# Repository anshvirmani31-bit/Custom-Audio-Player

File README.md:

# Custom-Audio-Player
Plays custom audio when you touch/click certain parts and things. The auido files it plays must be compressed as there is no external sd card slot, it is based of an esp32

# What is it?

This is a small audio file player with it's own standalone speaker based of an ESP-32-S3-WROOM-1. You can insert your own audio files however it has no external SD card slot meaning you only get the amount of local storage available on the ESP-32. This could be a potential downside because your file(s) will have to be heavily compressed. The reason I chose to design it like this is to keep the cost down and simpler to design.

# Images

## Schematic

### Full Schematic

### Oled Screen

### Rotary Encoder

### Voltage Regulator

### Audio Amplifier

### ESP32

### Receptacle

### Capacitive Touch Pads

### Cherry MX Button

## PCB

### Full Pcb

### 3D View

#### Front

#### Back

# BOM

|Item                       |Qty|Supplier  |Cost/item|Total Cost|link                                                 |
|---------------------------|---|----------|---------|----------|-----------------------------------------------------|
|ESP32-S3-WROOM1            |1  |AliExpress|$1.09    |$1.09     |https://www.aliexpress.com/item/1005010196291979.html|
|AP2112K-3.3TRG1            |1  |AliExpress|$1.89    |$1.89     |https://www.aliexpress.com/item/1005009023441155.html|
|MAX98357AETE+T             |1  |AliExpress|$6.44    |$6.44     |https://www.aliexpress.com/item/1005013004267095.html|
|USB Connector Type C Female|1  |AliExpress|$4.81    |$4.81     |https://www.aliexpress.com/item/1005013012638787.html|
|Rotary Encoder             |1  |AliExpress|$1.91    |$1.91     |https://www.aliexpress.com/item/1005007644083514.html|
|4 ohm Speaker              |1  |AliExpress|$2.28    |$2.28     |https://www.aliexpress.com/item/1005008626624201.html|
|Resistors                  |1  |AliExpress|$4.75    |$4.75     |https://www.aliexpress.com/item/1005012948787921.html|
|PCB                        |1  |JLCPCB    |$4.00    |$4.00     |https://jlcpcb.com                                   |
|OLED                       |1  |AliExpress|$2.55    |$2.55     |https://www.aliexpress.com/item/1005005692457058.html|
|Estimated total shipping   |1  |          |         |$1.50     |                                                     |

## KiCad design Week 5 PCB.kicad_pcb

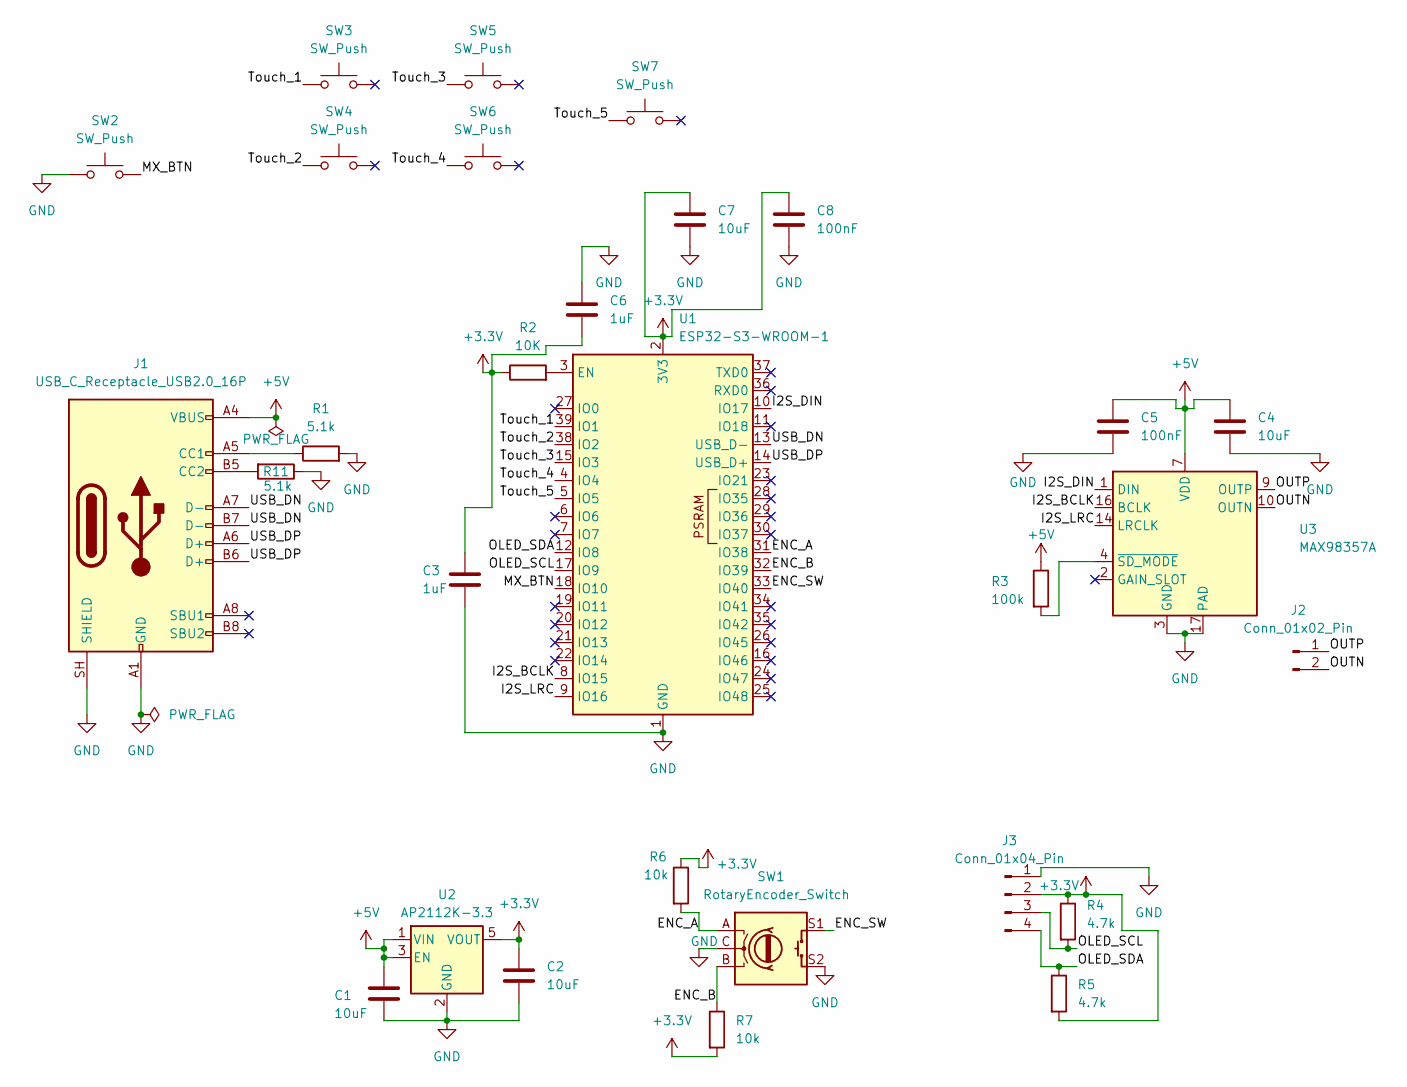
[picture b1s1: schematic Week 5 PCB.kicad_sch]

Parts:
C1, C2, C4, C7: 10uF; C_0805_2012Metric
C3, C6: 1uF; C_0805_2012Metric
C5, C8: 100nF; C_0805_2012Metric
J1: USB_C_Receptacle_USB2.0_16P; USB_C_Receptacle_HRO_TYPE-C-31-M-12
J2: Conn_01x02_Pin; PinHeader_1x02_P2.54mm_Vertical
J3: Conn_01x04_Pin; PinHeader_1x04_P2.54mm_Vertical
R1, R11: 5.1k; R_0805_2012Metric
R2: 10K; R_0805_2012Metric
R3: 100k; R_0805_2012Metric
R4, R5: 4.7k; R_0805_2012Metric
R6, R7: 10k; R_0805_2012Metric
SW1: RotaryEncoder_Switch; RotaryEncoder_Alps_EC11E-Switch_Vertical_H20mm
SW2: SW_Push; SW_Cherry_MX_1.00u_PCB
SW3, SW4, SW5, SW6, SW7: SW_Push; Single Touchpad
U1: ESP32-S3-WROOM-1
U2: AP2112K-3.3; SOT-23-5
U3: MAX98357A; TQFN-16-1EP_3x3mm_P0.5mm_EP1.23x1.23mm

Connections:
+3.3V: C2.1, C3.1, C6.2, C7.1, C8.1, J3.2, R2.1, R4.1, R5.2, R6.1, R7.2, U1.2 (3V3), U2.5 (VOUT)
+5V: C1.1, C4.1, C5.1, J1.A4 (VBUS), J1.A9 (VBUS), J1.B4 (VBUS), J1.B9 (VBUS), R3.1, U2.1 (VIN), U2.3 (EN), U3.7 (VDD), U3.8 (VDD)
/ENC_A: R6.2, SW1.A, U1.31 (IO38)
/ENC_B: R7.1, SW1.B, U1.32 (IO39)
/ENC_SW: SW1.S1, U1.33 (IO40)
/I2S_BCLK: U1.8 (IO15), U3.16 (BCLK)
/I2S_DIN: U1.10 (IO17), U3.1 (DIN)
/I2S_LRC: U1.9 (IO16), U3.14 (LRCLK)
/MX_BTN: SW2.2, U1.18 (IO10)
/OLED_SCL: J3.3, R4.2, U1.17 (IO9)
/OLED_SDA: J3.4, R5.1, U1.12 (IO8)
/OUTN: J2.2, U3.10 (OUTN)
/OUTP: J2.1, U3.9 (OUTP)
/Touch_1: SW3.1 (1_1), U1.39 (IO1)
/Touch_2: SW4.1 (1_1), U1.38 (IO2)
/Touch_3: SW5.1 (1_1), U1.15 (IO3)
/Touch_4: SW6.1 (1_1), U1.4 (IO4)
/Touch_5: SW7.1 (1_1), U1.5 (IO5)
/USB_DN: J1.A7 (D-), J1.B7 (D-), U1.13 (USB_D-)
/USB_DP: J1.A6 (D+), J1.B6 (D+), U1.14 (USB_D+)
GND: C1.2, C2.2, C3.2, C4.2, C5.2, C6.1, C7.2, C8.2, J1.A1 (GND), J1.A12 (GND), J1.B1 (GND), J1.B12 (GND), J1.SH (SHIELD), J3.1, R1.2, R11.1, SW1.C, SW1.S2, SW2.1, U1.1 (GND), U1.40 (GND), U1.41 (GND), U2.2 (GND), U3.3 (GND), U3.11 (GND), U3.15 (GND), U3.17 (PAD)
unnamed: J1.A5 (CC1), R1.1
unnamed: J1.B5 (CC2), R11.2
unnamed: R2.2, U1.3 (EN)
unnamed: R3.2, U3.4 (~SD_MODE)

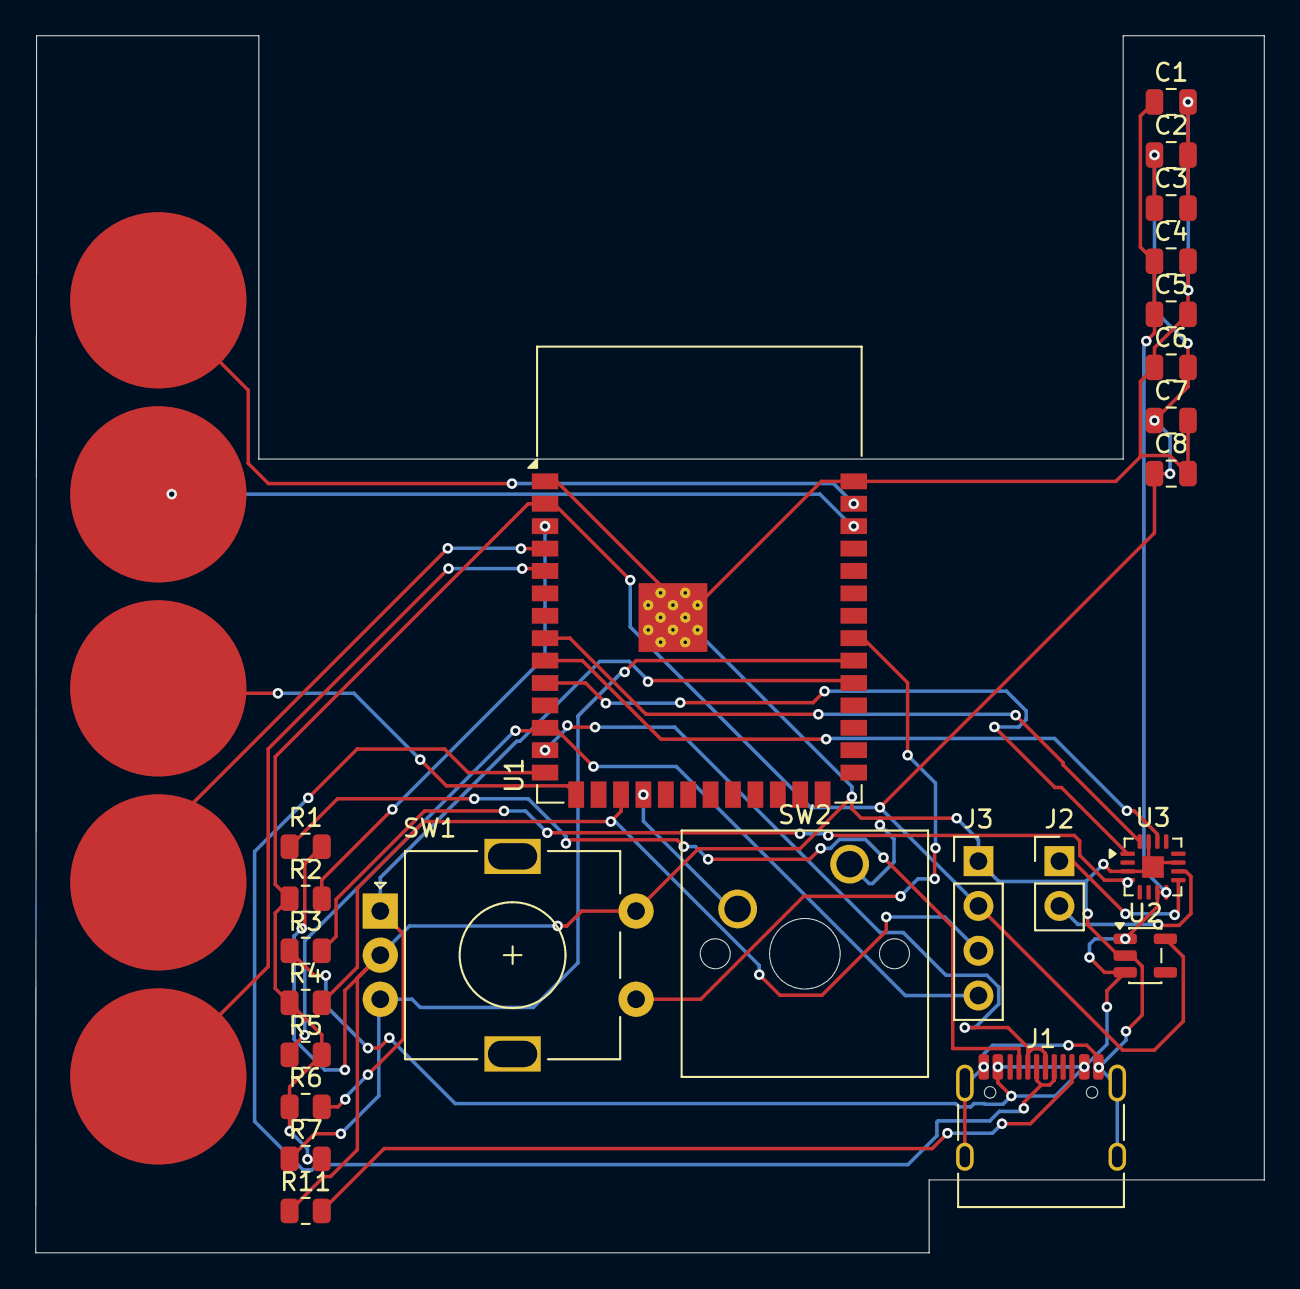
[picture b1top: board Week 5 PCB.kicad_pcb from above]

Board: 2 copper layers, 69.7 x 69.0 mm, 29 parts (0 on the bottom side), 25 nets.

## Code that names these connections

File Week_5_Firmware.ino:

#include <Arduino.h>
#include <Wire.h>
#include <LittleFS.h>
#include <Adafruit_GFX.h>
#include <Adafruit_SSD1306.h>
#include <ESP32Encoder.h>
#include "Audio.h"

// 1. Pin appointing

// MAX98357A I2S Amplifier (U3)
#define I2S_BCLK      15  // Pin 8 on U1 -> I2S_BCLK
#define I2S_LRC       16  // Pin 9 on U1 -> I2S_LRC
#define I2S_DOUT      17  // Pin 10 on U1 -> I2S_DIN

// Rotary Encoder (SW1)
#define ENC_A         38  // Pin 31 on U1 -> ENC_A
#define ENC_B         39  // Pin 32 on U1 -> ENC_B
#define ENC_SW        40  // Pin 33 on U1 -> ENC_SW

// Cherry MX Mechanical Switch (SW2)
#define MX_BTN_PIN    10  // Pin 18 on U1 -> MX_BTN

// I2C OLED Display (J3)
#define OLED_SDA      8   // Pin 12 on U1 -> OLED_SDA
#define OLED_SCL      9   // Pin 13 on U1 -> OLED_SCL
#define SCREEN_WIDTH  128
#define SCREEN_HEIGHT 64
#define OLED_ADDR     0x3C

// 5 Capacitive Touch Pads (SW3 - SW7)
const int TOUCH_PINS[5] = {1, 2, 3, 4, 5}; // IO1..IO5
const char* SOUND_FILES[5] = {
  "/sound1.mp3",
  "/sound2.mp3",
  "/sound3.mp3",
  "/sound4.mp3",
  "/sound5.mp3"
};
const char* SOUND_NAMES[5] = {
  "Pad 1: Track 1",
  "Pad 2: Track 2",
  "Pad 3: Track 3",
  "Pad 4: Track 4",
  "Pad 5: Track 5"
};

// 2. Objects
Audio audio;
ESP32Encoder encoder;
Adafruit_SSD1306 display(SCREEN_WIDTH, SCREEN_HEIGHT, &Wire, -1);

int currentVolume = 12;          // Range: 0 to 21
int savedVolume = 12;            // Stores pre-mute volume
bool isMuted = false;
const int MAX_VOLUME = 21;
long lastEncoderPos = 0;

String currentTrack = "Ready";
bool oledAvailable = false;

uint32_t touchBaseline[5];
const uint32_t TOUCH_DELTA = 15000; // Adjust after checking Serial Monitor
bool padPressed[5] = {false, false, false, false, false};

unsigned long lastBtnTime = 0;

// 3. OLED UI

void updateOLED() {
  if (!oledAvailable) return;

  display.clearDisplay();
  display.setTextColor(SSD1306_WHITE);

  // Header
  display.setTextSize(1);
  display.setCursor(0, 0);
  display.println("ESP32-S3 SOUNDPAD");
  display.drawLine(0, 10, 128, 10, SSD1306_WHITE);

  // Active Track Status
  display.setCursor(0, 18);
  display.print("Status: ");
  display.println(audio.isRunning() ? "Playing" : "Idle");

  display.setCursor(0, 30);
  display.println(currentTrack);

  // Volume Label & Percentage
  display.setCursor(0, 44);
  if (isMuted) {
    display.print("Vol: MUTED");
  } else {
    int volPct = map(currentVolume, 0, MAX_VOLUME, 0, 100);
    display.printf("Vol: %d%%", volPct);
  }

  // Volume Progress Bar
  display.drawRect(0, 54, 128, 10, SSD1306_WHITE);
  if (!isMuted && currentVolume > 0) {
    int barWidth = map(currentVolume, 0, MAX_VOLUME, 0, 124);
    display.fillRect(2, 56, barWidth, 6, SSD1306_WHITE);
  }

  display.display();
}

// 4. SETUP

void setup() {
  Serial.begin(115200);
  delay(500);

  // I2C & OLED
  Wire.begin(OLED_SDA, OLED_SCL);
  if (display.begin(SSD1306_SWITCHCAPVCC, OLED_ADDR)) {
    oledAvailable = true;
    display.clearDisplay();
    display.setTextSize(1);
    display.setTextColor(SSD1306_WHITE);
    display.setCursor(0, 24);
    display.println("Calibrating Pads...");
    display.display();
  } else {
    Serial.println("OLED not detected on J3 (continuing without screen)");
  }

  // Internal Flash Filesystem (LittleFS)
  if (!LittleFS.begin(true)) {
    Serial.println("LittleFS Mount Failed!");
    while (true);
  }

  // Switches (SW2 has no external pull-up, ENC_SW has internal pull-up)
  pinMode(MX_BTN_PIN, INPUT_PULLUP);
  pinMode(ENC_SW, INPUT_PULLUP);

  // Hardware Rotary Encoder (External 10k pull-ups on R6, R7)
  encoder.attachHalfQuad(ENC_A, ENC_B);
  encoder.setCount(currentVolume * 2);
  lastEncoderPos = currentVolume;

  // I2S Audio
  audio.setPinout(I2S_BCLK, I2S_LRC, I2S_DOUT);
  audio.setVolume(currentVolume);

  // Auto-Calibrate 5 Touch Pads
  Serial.println("Calibrating capacitive touch pads...");
  for (int i = 0; i < 5; i++) {
    uint64_t sum = 0;
    for (int s = 0; s < 25; s++) {
      sum += touchRead(TOUCH_PINS[i]);
      delay(10);
    }
    touchBaseline[i] = sum / 25;
    Serial.printf("Touch_%d (IO%d) Baseline: %lu\n", i + 1, TOUCH_PINS[i], touchBaseline[i]);
  }

  updateOLED();
  Serial.println("System Ready!");
}

// 5. MAIN LOOP

void loop() {
  audio.loop();

  // 1. Rotary Encoder Volume Control
  long newPos = encoder.getCount() / 2;
  if (newPos != lastEncoderPos) {
    int diff = newPos - lastEncoderPos;
    if (isMuted) {
      isMuted = false;
      currentVolume = savedVolume;
    }
    currentVolume = constrain(currentVolume + diff, 0, MAX_VOLUME);
    encoder.setCount(currentVolume * 2);
    lastEncoderPos = currentVolume;

    audio.setVolume(currentVolume);
    Serial.printf("Volume: %d / %d\n", currentVolume, MAX_VOLUME);
    updateOLED();
  }

  // --- 2. Push Button (Mute / Unmute Toggle)
  if (digitalRead(ENC_SW) == LOW && (millis() - lastBtnTime > 250)) {
    lastBtnTime = millis();
    isMuted = !isMuted;
    if (isMuted) {
      savedVolume = currentVolume;
      audio.setVolume(0);
      Serial.println("Muted");
    } else {
      currentVolume = savedVolume;
      audio.setVolume(currentVolume);
      Serial.printf("Unmuted (Vol: %d)\n", currentVolume);
    }
    updateOLED();
  }

  // 3. Cherry MX Switch (Stop Playback)
  if (digitalRead(MX_BTN_PIN) == LOW && (millis() - lastBtnTime > 250)) {
    lastBtnTime = millis();
    if (audio.isRunning()) {
      audio.stopSong();
      currentTrack = "Stopped";
      Serial.println("Stopped via MX_BTN");
      updateOLED();
    }
  }

  // 4. 5 Capacitive Touch Pads
  for (int i = 0; i < 5; i++) {
    uint32_t val = touchRead(TOUCH_PINS[i]);

    if (val > (touchBaseline[i] + TOUCH_DELTA)) {
      if (!padPressed[i]) {
        padPressed[i] = true;
        currentTrack = SOUND_NAMES[i];
        Serial.printf("Touch_%d triggered! (Val: %lu) -> %s\n", i + 1, val, SOUND_FILES[i]);
        audio.connecttoFS(LittleFS, SOUND_FILES[i]);
        updateOLED();
      }
    } else if (val < (touchBaseline[i] + (TOUCH_DELTA / 2))) {
      padPressed[i] = false;
    }
  }
}

// Optional callback when a track finishes playing naturally
void audio_eof_mp3(const char *info) {
  currentTrack = "Finished";
  updateOLED();
}
